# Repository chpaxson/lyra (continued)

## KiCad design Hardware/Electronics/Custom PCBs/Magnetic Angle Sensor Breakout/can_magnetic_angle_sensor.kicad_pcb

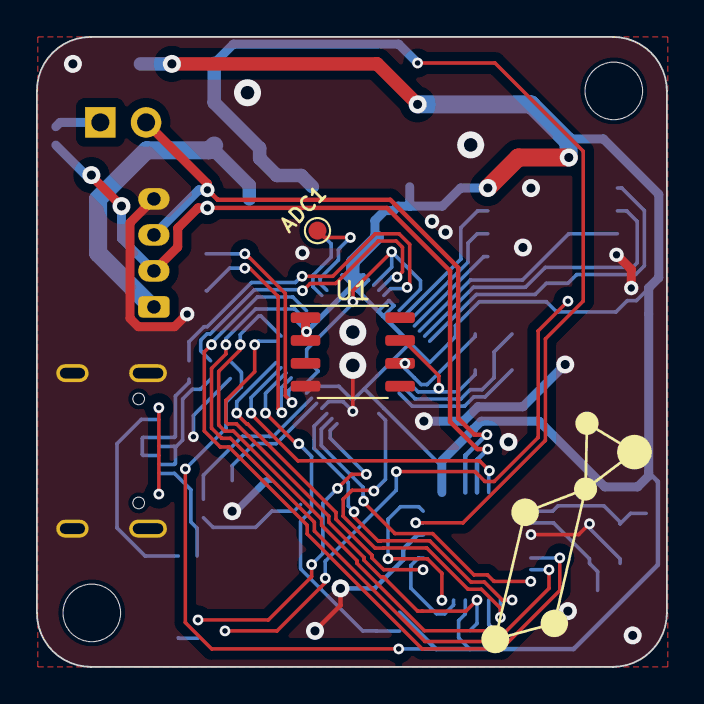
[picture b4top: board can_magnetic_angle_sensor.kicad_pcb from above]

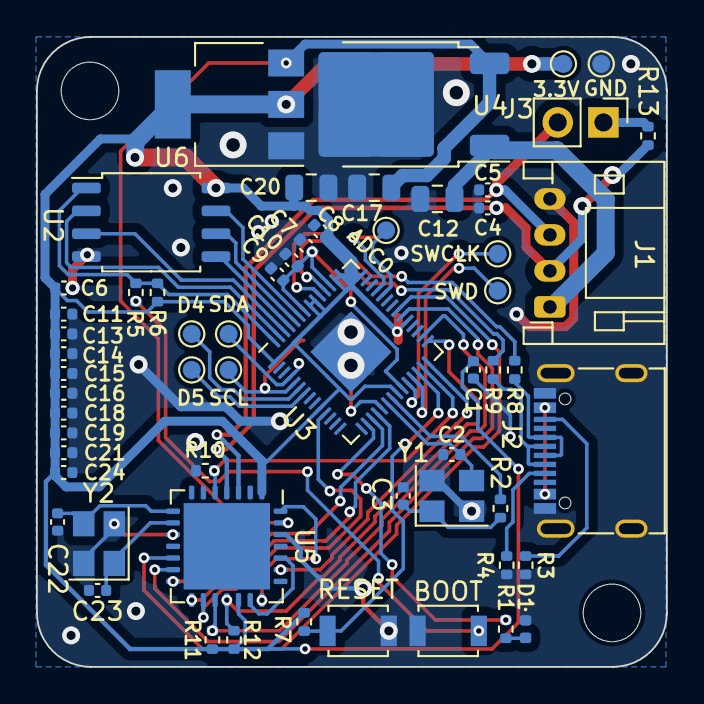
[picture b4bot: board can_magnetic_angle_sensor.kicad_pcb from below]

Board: 2 copper layers, 35.0 x 35.0 mm, 63 parts (59 on the bottom side), 49 nets.

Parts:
3.3V: 3.3V; TestPoint_Pad_D1.0mm
ADC0: ADC0; TestPoint_Pad_D1.0mm
ADC1: ADC1; TestPoint_Pad_D1.0mm
BOOT: USB_BOOT; SW_SPST_B3U-1000P
C1: 0.1u; C_0402_1005Metric
C2, C3, C22, C23: 22p; C_0402_1005Metric
C4, C5: 47p; C_0402_1005Metric
C6, C9, C10, C11, C13, C14, C15, C16, C18, C19, C21, C24: 100n; C_0402_1005Metric
C7, C8: 1u; C_0402_1005Metric
C12: 0.33u/50V; C_0805_2012Metric
C17, C20: 10u; C_0805_2012Metric
D1: LED; LED_0402_1005Metric
D4: D4; TestPoint_Pad_D1.0mm
D5: D5; TestPoint_Pad_D1.0mm
GND: GND; TestPoint_Pad_D1.0mm
H1, H2: MountingHole; MountingHole_3.2mm_M3_DIN965
J1: JST PH 01x04; JST_PH_S4B-PH-K_1x04_P2.00mm_Horizontal
J2: USB C Receptacle; USB_C_Receptacle_G-Switch_GT-USB-7010ASV
J3: 120TR; PinHeader_1x02_P2.54mm_Vertical
R1, R7, R10, R11, R12: 10k; R_0402_1005Metric
R2: 1k; R_0402_1005Metric
R3, R4: 5.1k; R_0402_1005Metric
R5: 1K; R_0402_1005Metric
R6: 10K; R_0402_1005Metric
R8, R9: 27; R_0402_1005Metric
R13: 120; R_0402_1005Metric
RESET: RESET; SW_SPST_B3U-1000P
SCL: SCL; TestPoint_Pad_D1.0mm
SDA: SDA; TestPoint_Pad_D1.0mm
SWCLK: SWCLK; TestPoint_Pad_D1.0mm
SWD: SWD; TestPoint_Pad_D1.0mm
U1: MT6701-CT; SOP-8_3.9x4.9mm_P1.27mm
U2: W25Q128JVS; SOIC-8_5.23x5.23mm_P1.27mm
U3: RP2040; QFN-56-1EP_7x7mm_P0.4mm_EP3.2x3.2mm
U4: KA78M05_TO252; TO-252-2
U5: MCP25625-x-SS; QFN-28-1EP_6x6mm_P0.65mm_EP4.8x4.8mm
U6: NCP1117-3.3_SOT223; SOT-223-3_TabPin2
Y1: 12MHz/12pF; Crystal_SMD_3225-4Pin_3.2x2.5mm
Y2: 16MHz/12pF; Crystal_SMD_3225-4Pin_3.2x2.5mm

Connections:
+1V1: C7.1, C9.1, C10.1, U3.23 (DVDD), U3.45 (VREG_VOUT), U3.50 (DVDD)
+3.3V: 3.3V.1, C1.1, C6.1, C8.2, C11.2, C13.2, C14.2, C15.2, C16.2, C18.2, C19.2, C20.1, C21.2, C24.2, R6.2, R7.1, R11.1, R12.1, U1.1 (VDD), U1.2 (MODE), U2.8 (VCC), U3.1 (IOVDD), U3.10 (IOVDD), U3.22 (IOVDD), U3.33 (IOVDD), U3.42 (IOVDD), U3.43 (ADC_AVDD), U3.44 (VREG_IN), U3.48 (USB_VDD), U3.49 (IOVDD), U5.1 (VIO), U5.19 (VDD), U6.2 (VO)
+5V: C17.1, U4.3 (VO), U5.27 (VDDA), U6.3 (VI)
+24V: C12.1, J1.1, U4.1 (VI)
/CAN_CS: R11.2, U3.30 (GPIO19), U5.17 (~CS)
/CAN_H: C4.1, J1.2, R13.2, U5.4 (CANH)
/CAN_INT: U3.34 (GPIO22), U5.13 (~INT)
/CAN_L: C5.1, J1.3, J3.2, U5.3 (CANL)
/CAN_RESET: R12.2, U3.29 (GPIO18), U5.18 (~RESET)
/CAN_STBY: R10.2, U3.27 (GPIO16), U5.5 (STBY)
/LED: R1.2, U3.16 (GPIO13)
/MISO: U3.11 (GPIO8), U5.16 (SO)
/MOSI: U3.18 (GPIO15), U5.15 (SI)
/QSPI_SCK: U2.6 (CLK), U3.52 (QSPI_SCLK)
/QSPI_SD0: U2.5 (DI(IO0)), U3.53 (QSPI_SD0)
/QSPI_SD1: U2.2 (DO(IO1)), U3.55 (QSPI_SD1)
/QSPI_SD2: U2.3 (IO2), U3.54 (QSPI_SD2)
/QSPI_SD3: U2.7 (IO3), U3.51 (QSPI_SD3)
/QSPI_SS: R5.2, R6.1, U2.1 (~CS), U3.56 (QSPI_SS)
/RUN: R7.2, RESET.2, U3.26 (RUN)
/RX0BF: U3.35 (GPIO23), U5.12 (~Rx0BF)
/SCK: U3.17 (GPIO14), U5.14 (SCK)
/SCL: SCL.1, U1.7 (B/V/SCL/CLK), U3.5 (GPIO3)
/SDA: SDA.1, U1.6 (A/U/SDA/DO), U3.4 (GPIO2)
/TX0RTS: U3.28 (GPIO17), U5.23 (~Tx0RTS)
/USB_D+: J2.A6 (D+), J2.B6 (D+), R8.1
/USB_D-: J2.A7 (D-), J2.B7 (D-), R9.1
/XIN: C2.2, U3.20 (XIN), Y1.3
/XOUT: R2.2, U3.21 (XOUT)
/~USB_BOOT: BOOT.2, R5.1
GND: BOOT.1, C1.2, C2.1, C3.1, C4.2, C5.2, C6.2, C7.2, C8.1, C9.2, C10.2, C11.1, C12.2, C13.1, C14.1, C15.1, C16.1, C17.2, C18.1, C19.1, C20.2, C21.1, C22.2, C23.2, C24.1, D1.1 (K), GND.1, J1.4, J2.A1 (GND), J2.A12 (GND), J2.B1 (GND), J2.B12 (GND), J2.S1 (SHIELD), R3.2, R4.2, R10.1, RESET.1, U1.4 (GND), U2.4 (GND), U3.19 (TESTEN), U3.57 (GND), U4.2 (GND), U5.10 (GND), U5.26 (VSS), U6.1 (GND), Y1.2, Y1.4, Y2.2, Y2.4
unnamed: C3.2, R2.1, Y1.1
unnamed: D1.2 (A), R1.1
unnamed: J2.A5 (CC1), R4.1
unnamed: J2.B5 (CC2), R3.1
unnamed: J3.1, R13.1
unnamed: D4.1, U3.6 (GPIO4)
unnamed: D5.1, U3.7 (GPIO5)
unnamed: ADC0.1, U3.38 (GPIO26_ADC0)
unnamed: ADC1.1, U3.39 (GPIO27_ADC1)
unnamed: SWCLK.1, U3.24 (SWCLK)
unnamed: SWD.1, U3.25 (SWD)
unnamed: R9.2, U3.46 (USB_DM)
unnamed: R8.2, U3.47 (USB_DP)
unnamed: C23.1, U5.9 (OSC1), Y2.1
unnamed: C22.1, U5.8 (OSC2), Y2.3
unnamed: U5.21 (RxCAN), U5.28 (RXD)
unnamed: U5.20 (TxCAN), U5.24 (TXD)
VBUS: J2.A4 (VBUS), J2.A9 (VBUS), J2.B4 (VBUS), J2.B9 (VBUS)

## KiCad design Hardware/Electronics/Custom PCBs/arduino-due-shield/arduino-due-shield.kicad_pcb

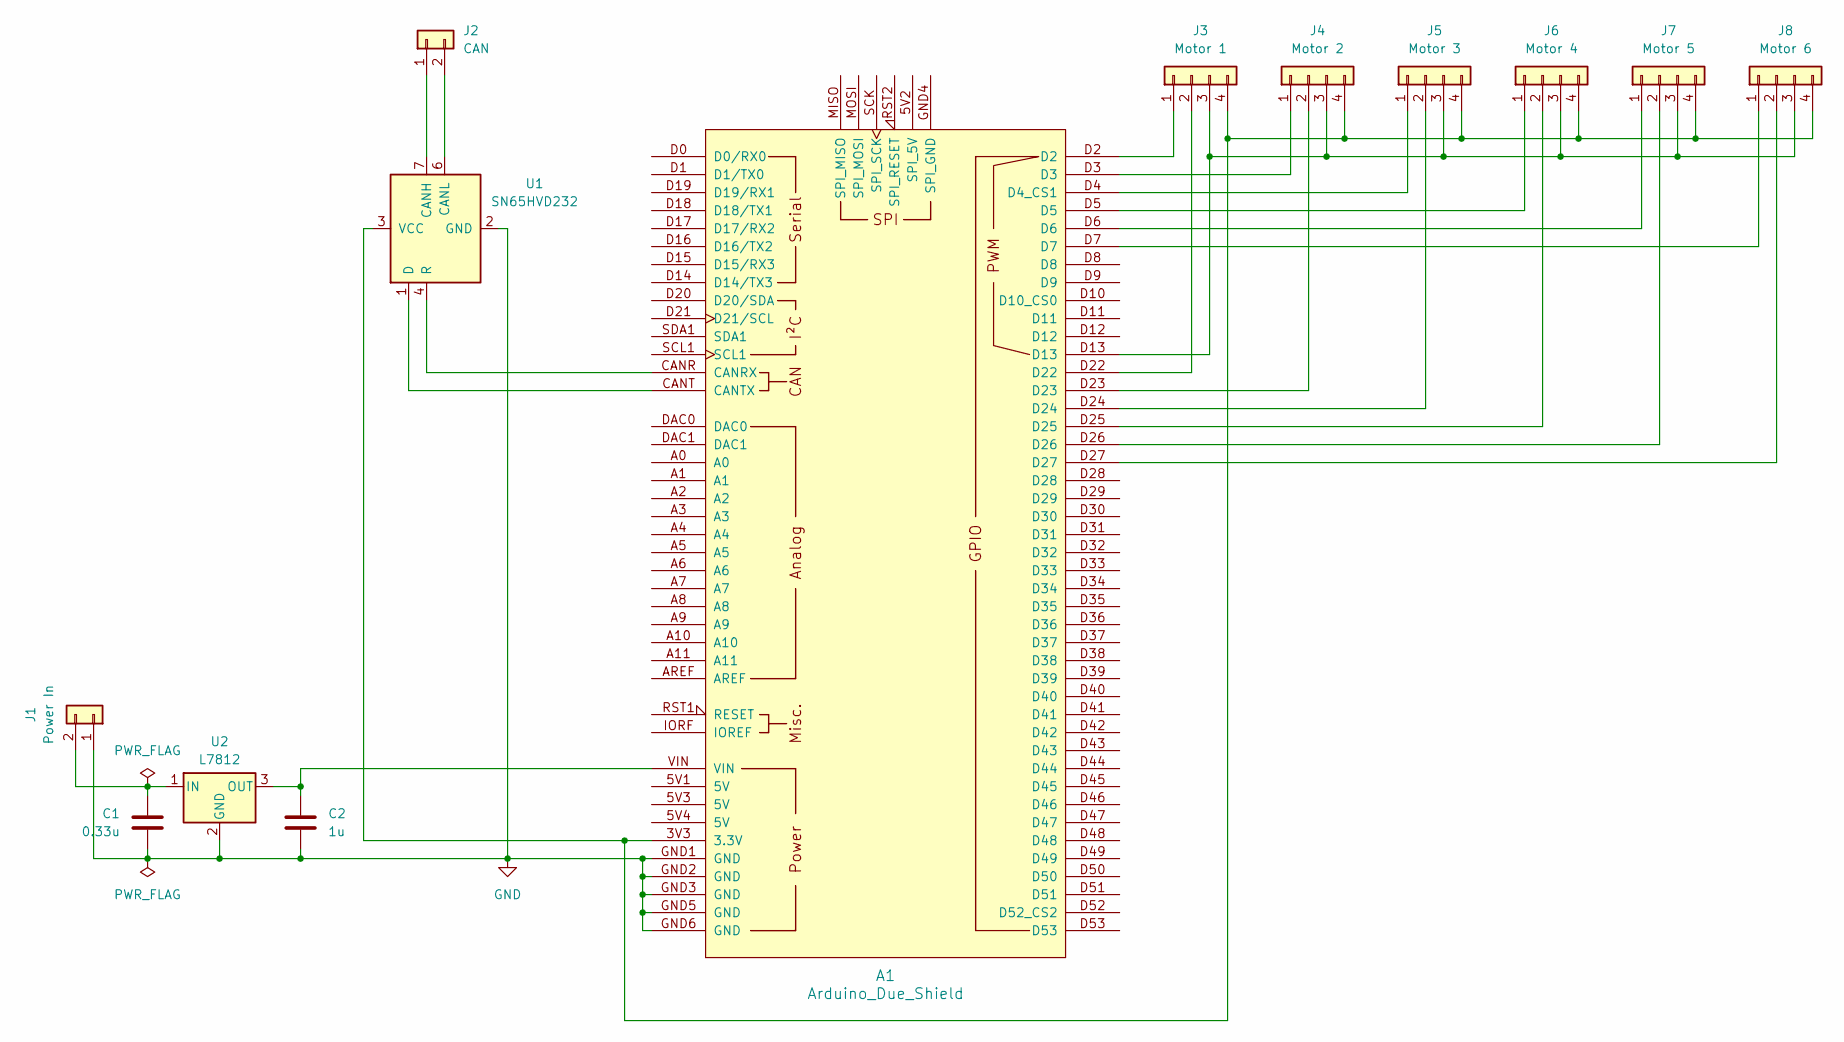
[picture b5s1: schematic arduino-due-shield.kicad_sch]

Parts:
A1: Arduino_Due_Shield
C1: 0.33u; C_0603_1608Metric_Pad1.08x0.95mm_HandSolder
C2: 1u; C_0603_1608Metric_Pad1.08x0.95mm_HandSolder
J1: Power In; AMASS_XT30U-F_1x02_P5.0mm_Vertical
J2: CAN; JST_PH_B2B-PH-K_1x02_P2.00mm_Vertical
J3: Motor 1; JST_PH_B4B-PH-K_1x04_P2.00mm_Vertical
J4: Motor 2; JST_PH_B4B-PH-K_1x04_P2.00mm_Vertical
J5: Motor 3; JST_PH_B4B-PH-K_1x04_P2.00mm_Vertical
J6: Motor 4; JST_PH_B4B-PH-K_1x04_P2.00mm_Vertical
J7: Motor 5; JST_PH_B4B-PH-K_1x04_P2.00mm_Vertical
J8: Motor 6; JST_PH_B4B-PH-K_1x04_P2.00mm_Vertical
U1: SN65HVD232; SOIC-8_3.9x4.9mm_P1.27mm
U2: L7812; TO-263-2

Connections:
GND: A1.GND1 (GND), A1.GND2 (GND), A1.GND3 (GND), A1.GND5 (GND), A1.GND6 (GND), C1.1, C2.2, J1.1, U1.2 (GND), U2.2 (GND)
unnamed: A1.3V3 (3.3V), J3.4, J4.4, J5.4, J6.4, J7.4, J8.4, U1.3 (VCC)
unnamed: A1.CANR (CANRX), U1.4 (R)
unnamed: A1.CANT (CANTX), U1.1 (D)
unnamed: A1.D4 (D4_CS1), J5.1
unnamed: A1.D2, J3.1
unnamed: A1.D3, J4.1
unnamed: A1.D5, J6.1
unnamed: A1.D6, J7.1
unnamed: A1.D7, J8.1
unnamed: A1.D13, J3.3, J4.3, J5.3, J6.3, J7.3, J8.3
unnamed: A1.D22, J3.2
unnamed: A1.D23, J4.2
unnamed: A1.D24, J5.2
unnamed: A1.D25, J6.2
unnamed: A1.D26, J7.2
unnamed: A1.D27, J8.2
unnamed: C1.2, J1.2, U2.1 (IN)
unnamed: J2.1, U1.7 (CANH)
unnamed: J2.2, U1.6 (CANL)
unnamed: A1.VIN, C2.1, U2.3 (OUT)

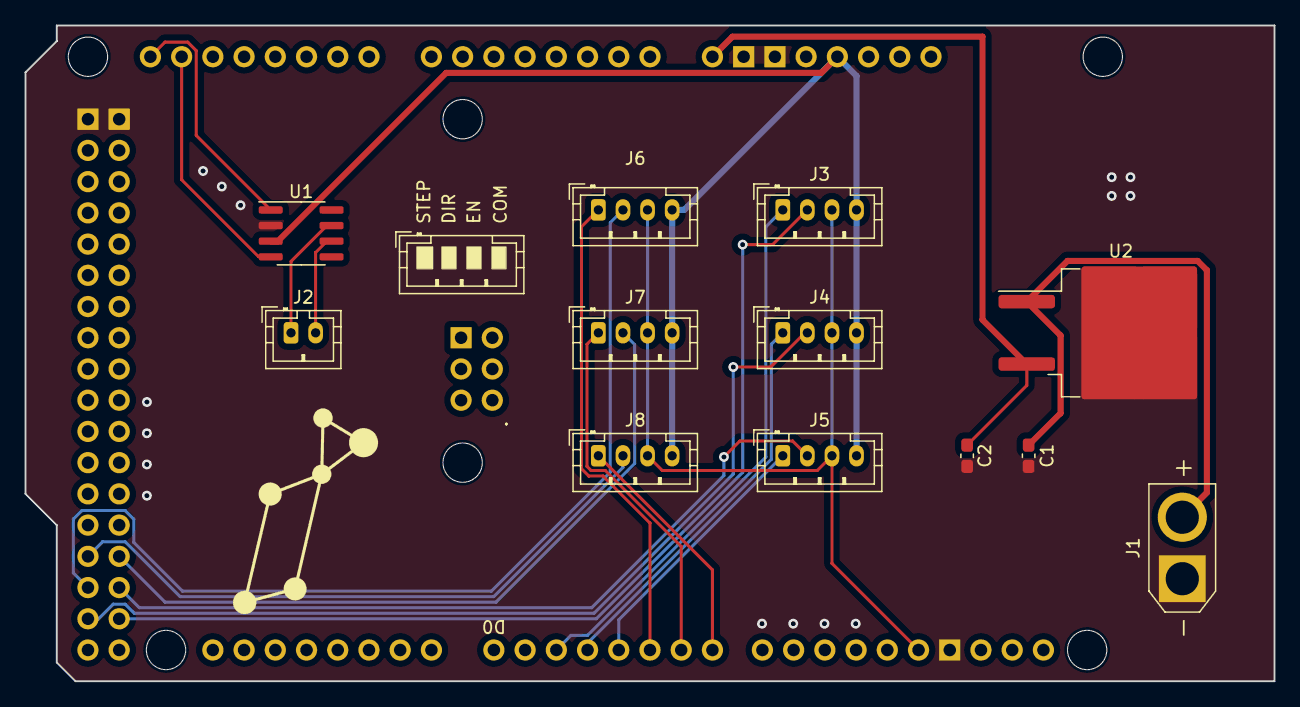
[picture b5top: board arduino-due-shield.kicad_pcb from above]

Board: 2 copper layers, 101.6 x 53.3 mm, 13 parts (0 on the bottom side), 21 nets.

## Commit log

2024-01-15 Mockups & joint 2 gearbox
    Also begins the joint 3 gearbox
2024-01-16 More for Joint 3
2024-01-16 Update Joint 3
2024-01-17 Update Joint 4
2024-01-18 Joint 4 Cycloidal Disk
2024-01-18 Create final assembly file
2024-01-23 Change mockup arm 2-3 name to prevent file name mixups
2024-01-23 CAN Testing
2024-01-24 Functioning CAN driver
2024-01-25 Progress on NEMA17 gearbox
2024-01-25 Add gearbox output heat set insert holes
2024-01-26 Create Joint 1
    Yeth
2024-01-26 Update NEMA17 Gearbox
2024-01-26 NEMA17 Gearbox Finishing Touches
2024-01-27 NEMA17 Gearbox Finishing Touches 2
2024-01-28 Updates
    Finalized Joint 2-3 arm
    Updated can_driver.py
    Updated Joint 2 Eccentric Shaft input coupler bore
2024-01-30 Update Joint 2 tolerances
2024-02-04 Modify Joint 2 eccentric shaft motor coupling solution
2024-02-04 Update folder structure part 1
2024-02-04 Update files to SW 2023 and finish reorganization
2024-02-07 Update to SW 2023
2024-02-14 Joint 1
    These are the components for Joint 1 of Lyra.
2024-02-16 Update mockup forearm size
2024-02-20 JOINT 5 AND 6
2024-02-20 Update File Structure
2024-02-20 Fix Joint 5+6 dependencies
2024-02-20 Joint 5 + 6
2024-02-20 Rename V3_2_Assembly.SLDASM to Joint5+6Assembly.SLDASM
2024-02-20 Fix Joint 5+6 dependencies again
2024-02-29 Joint 1 Update
    Hello
2024-02-29 Rearrange Joint 1 Files
2024-02-29 Planetary Gearbox V0.1
    Doesn't work due to the 20 tooth sun gear not being radially symmetric
2024-02-29 Make custom planet/sun gear
2024-02-29 Further progress on Joint 1, may need to change to a two-stage gearbox design
2024-03-01 Add secondary gear train
2024-03-01 Arduino Due Model
    https://grabcad.com/library/arduino-due-1
2024-03-02 Update joint 1 gear train
2024-03-02 Update Joint 1
2024-03-02 Add 70x90x10mm Bearing
2024-03-02 joint 4 update for slip ring
2024-03-02 Add Joint 1 Motor Housing
2024-03-02 Begin adding microcontroller
2024-03-02 Updated joint 5+6 V4 at this point hehe
2024-03-02 Version 4 now lolz
2024-03-02 Begin PCB design & rename some Joint 5+6 files
2024-03-03 Joint 4 motor housing modification
2024-03-03 Cap for slip ring and adjusted holes for threaded rods
2024-03-03 Complete Arduino Due Shield
2024-03-03 Updated it Charles LMK
2024-03-03 Begin Magnetic Angle Sensor
2024-03-04 Further progress on PCB
2024-03-04 Work on integrating Joint 4 a bit
2024-03-05 Create Magnetic Sensor V2 project
2024-03-05 Finish Joint 4 gearing
2024-03-06 UPDATE March 5th
2024-03-07 Further work on Joint 3/4
2024-03-07 V2 magnetic sensor work
2024-03-10 Finish CAN Magnetic Angle Sensor v2
2024-03-11 Work on Joint 1/2 and Joint 3/4 integration
2024-03-12 Small Updates
2024-03-13 Begin toolhead PCB design and prep Joints 2,3,4 for printing
2024-03-14 Work on Toolhead Board
2024-03-15 Update tolerances for printing, slice base, and begin Joint 5+6 V2
2024-03-16 Make some updates
2024-03-16 some updates
2024-03-16 Work on toolhead board more
2024-03-16 Remove locks
2024-03-16 Finish Toolhead Schematic
2024-03-16 small updated
2024-03-18 Create split Joint 4 housing for failed print
2024-03-29 Mounting design Added
    Ring Gear with mounting
2024-03-30 Updated Footprints
2024-03-30 Continue adding footprints
2024-03-30 Get basic Toolhead Board outline
2024-03-30 Begin layout and routing of toolhead board
2024-03-31 Update toolhead
2024-04-01 Update toolhead board layout
2024-04-01 Mounting Holes
2024-04-02 Update toolhead layout
2024-04-02 Update layout
2024-04-02 Toolhead Board Updated Traces
    Updated Traces, about half of the resistors are done and a few capacitors along with most mp components
2024-04-03 Updated PCB
2024-04-03 Updated PCB
    Added resistor traces for Servo stokes
2024-04-04 Update toolhead board yet again
2024-04-04 Update PCB
2024-04-05 Update base mounting
2024-04-05 Temp PCB
2024-04-05 Update layout slightly
2024-04-05 Begin replacing CAN transceiver
2024-04-07 Update toolhead schematic+layout and add tolerances to base
2024-04-08 Update more tolerances
2024-04-09 Update more tolerances in Joint 1
2024-04-09 Update toolhead PCB layout
2024-04-09 Update layout a bit more
2024-04-10 NEW Version
2024-04-12 updated PCB layout
2024-04-12 Fix DRC Problems
2024-04-12 one damn unconnected item
2024-04-12 final pcb layout
2024-04-12 Add basics of toolhead breakout
2024-04-13 Update Wrist Motor Design
2024-04-14 Updated Breakout Board Layout
2024-04-14 updated breakout board design
2024-04-15 Updated Breakout Board Layout
    Finished all the traces. Prior to adding LDO's from 24V to 5V.
2024-04-15 Add power supply and controller mounting
2024-04-16 updated breakout board design with added LDO's
2024-04-16 Begin software development
2024-04-16 Configure ROS workspace
2024-04-16 updated breakout board
    LDO footprint
2024-04-16 Finished Breakout Board
2024-04-17 Create End Effector
    File for the design of the end effector.
2024-04-17 Breakout Board fix
    About 60% finished but need some help
2024-04-17 little updates on missing files
2024-04-18 Finish wrist motor mount and update breakout layout
2024-04-18 Finish breakout layout
2024-04-18 Export breakout PCB fabrication files and make wrist motor housing flippable
2024-04-18 Updated Breakout Board
2024-04-18 Updates from April 18th
2024-04-18 Create Gripper
    Design for the Lyra Gripper
2024-04-18 Create Gripper
    Design for Lyra Gripper
2024-04-18 Gripper Design
    Here is the design progress for the Lyra Gripper
2024-04-18 Gripper Design
    Here is the progress for the gripper design
2024-04-19 Update NEMA17 gearbox eccentric shaft
2024-04-19 updates from April 19
2024-04-19 Updated Gripper
    Added some mounting holes for the gripper hand and motor housing
2024-04-20 create joint 2 exploded view
2024-04-20 Updated Gripper Base and PCB Bay Assem.
2024-04-20 Gripper Base V1
2024-04-20 Updated Gripper Design
2024-04-21 made a change
2024-04-21 Updated Gripper Base
2024-04-21 Add upper wrist padding
2024-04-22 New Gripper Design
    Scrapped design for V0 and V1.
2024-04-22 Gripper Design
2024-04-22 Gripper Updated
2024-04-22 Gripper Base Updated
2024-04-22 finish final assembly for rendering
2024-04-22 Taking a stab at the control firmware
2024-04-22 basic demo movement
2024-04-22 Finalize presentation demo with acceleration
2024-04-23 Gripper is gripping
2024-04-23 Add Toolhead Board SOLIDWORKS Files
2024-04-23 Updated Gripper
2024-04-23 Cleaned Gripper Files
2024-04-23 Clean Files
2024-04-23 Restructure previous versions of Joints 3-6
2024-04-24 updated gripper and model of stepper motor
2024-04-25 fingers
2024-04-25 finger update
2024-04-26 Updated finger
2024-04-26 updated gripper with dovetail
2024-04-26 updated gripper v5
    charles your keybopard is really nice so i just want to type on it but it jis kinda weird
2024-04-26 Final Design Review for Gripper
2024-04-26 gripper
2024-04-26 Tolerance and DR of gripper V4
2024-04-26 pcb bay connections
2024-04-26 Tolerance & Finalize Gripper V4
